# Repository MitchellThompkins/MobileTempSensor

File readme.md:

## Description

This contains all of the required documents to create a handheld temperature and humidity sensor.

### Current revision of the PCB:

### The populated board and finished design:

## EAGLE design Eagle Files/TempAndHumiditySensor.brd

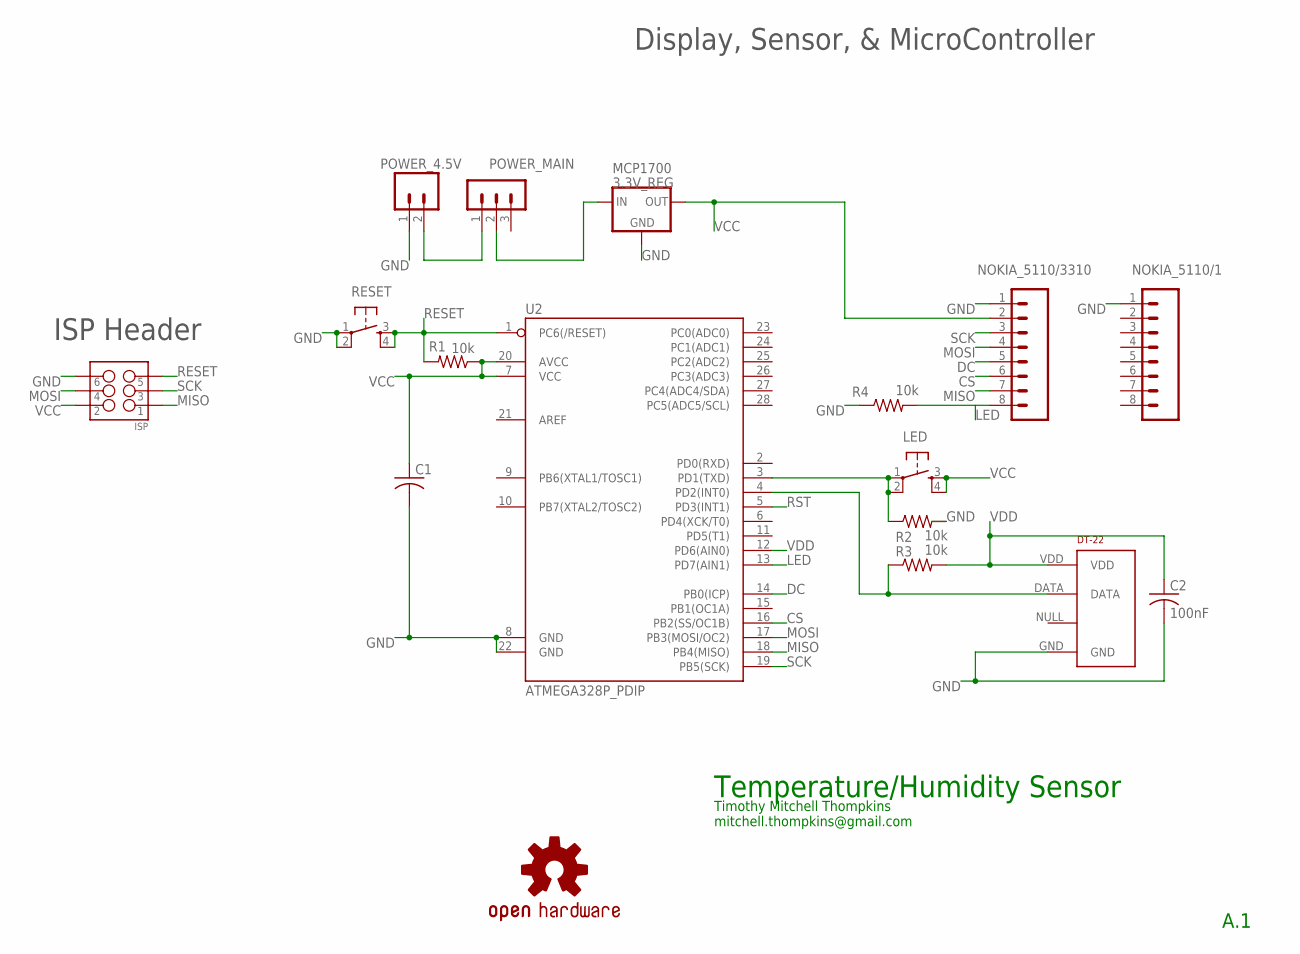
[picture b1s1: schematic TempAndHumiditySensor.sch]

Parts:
C1: C-US025-040X050; C025-040X050
C2: 100nF; C025-040X050
DT-22: RHT03_DHT-22_AM2302RA; RHT03_DHT-22/RA
ISP: M03X2POGO_PINS; 2X3_POGO
LED: RESET; TACTILE-PTH
LOGO2: OSHW-LOGOS; OSHW-LOGO-S
MCP1700: 3.3V_REG; TO92-INLINE
NOKIA_5110/1, NOKIA_5110/3310: M08; 1X08_PIN1_NO_SILK
POWER_4.5V: M02LOCK_LONGPADS; 1X02_LOCK_LONGPADS
POWER_MAIN: MA03-1
R1, R2, R3, R4: 10k; 0204/7
RESET: RESET; TACTILE-PTH
U2: ATMEGA328P_PDIP; DIL28-3

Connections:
CS: NOKIA_5110/3310.6, U2.16 (PB2(SS/OC1B))
DC: NOKIA_5110/3310.5, U2.14 (PB0(ICP))
GND: C1.2, C2.2, DT-22.GND, ISP.P$6 (6), MCP1700.1 (GND), NOKIA_5110/1.1, NOKIA_5110/3310.1, POWER_4.5V.1, R2.2, R4.1, RESET.1, RESET.2, U2.8 (GND), U2.22 (GND)
LED: NOKIA_5110/3310.8, R4.2, U2.13 (PD7(AIN1))
MISO: ISP.P$1 (1), NOKIA_5110/3310.7, U2.18 (PB4(MISO))
MOSI: ISP.P$4 (4), NOKIA_5110/3310.4, U2.17 (PB3(MOSI/OC2))
unnamed: POWER_4.5V.2, POWER_MAIN.1
unnamed: MCP1700.2 (IN), POWER_MAIN.2
unnamed: LED.1, LED.2, R2.1, U2.3 (PD1(TXD))
unnamed: DT-22.DATA, R3.1, U2.4 (PD2(INT0))
RESET: ISP.P$5 (5), R1.2, RESET.3, RESET.4, U2.1 (PC6(/RESET))
RST: U2.5 (PD3(INT1))
SCK: ISP.P$3 (3), NOKIA_5110/3310.3, U2.19 (PB5(SCK))
VCC: C1.1, ISP.P$2 (2), LED.3, LED.4, MCP1700.3 (OUT), NOKIA_5110/3310.2, R1.1, U2.7 (VCC), U2.20 (AVCC)
VDD: C2.1, DT-22.VDD, R3.2, U2.12 (PD6(AIN0))

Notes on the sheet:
Timothy Mitchell Thompkins mitchell.thompkins@gmail.com
Temperature/Humidity Sensor
A.1
ISP Header
Display, Sensor, & MicroController

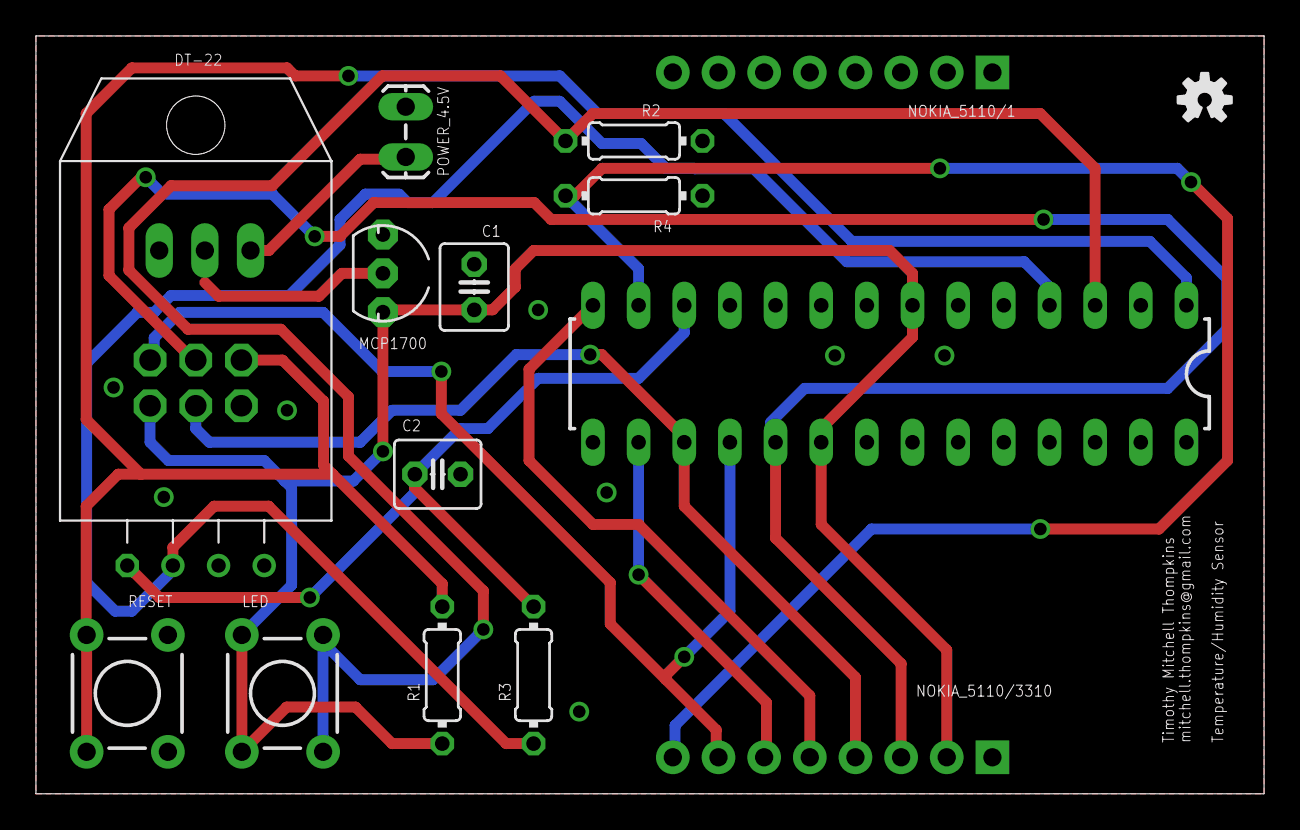
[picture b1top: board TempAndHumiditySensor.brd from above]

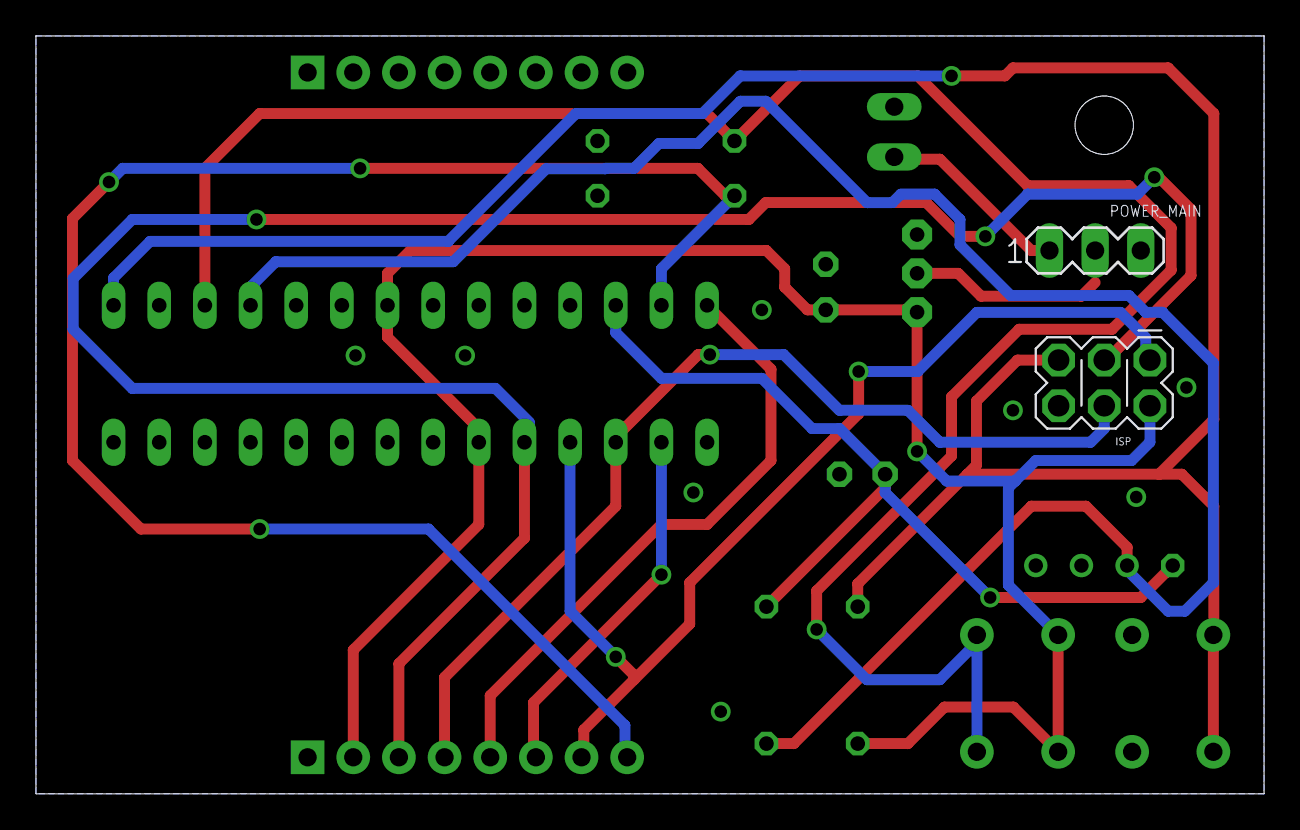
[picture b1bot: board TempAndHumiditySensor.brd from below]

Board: 2 copper layers, 68.3 x 42.2 mm, 17 parts (2 on the bottom side), 14 nets.

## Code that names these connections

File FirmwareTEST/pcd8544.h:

/*
 *
 * Name         :  pcd8544.h
 *
 * Description  :  This is header file for the PCD8544 graphic LCD driver.
 *                 Based on the code written by Sylvain Bissonette
 *
 * Author       :  Fandi Gunawan <fandigunawan@gmail.com>
 * Website      :  http://fandigunawan.wordpress.com
 *
 * Credit       :  Sylvain Bissonette (2003)
 *                 Louis Frigon (2003)
 *
 * License      :  GPL v. 3
 *
 * Compiler     :  WinAVR, GCC for AVR platform
 *                 Tested version :
 *                 - 20070525
 *                 - 20071221
 *                 - 20081225
 * Compiler note:  Please be aware of using older/newer version since WinAVR
 *                 is in extensive development. Please compile with parameter -O1
 *
 * History      :
 * Please refer to pcd8544.c
 */

#ifndef _PCD8544_H_
#define _PCD8544_H_

/* General constants for driver */
#define FALSE                      0
#define TRUE                       1

/* For return value */
#define OK                         0
#define OUT_OF_BORDER              1
#define OK_WITH_WRAP               2


#define LCD_X_RES                  84    /* x resolution */
#define LCD_Y_RES                  48    /* y resolution */
#define EMPTY_SPACE_BARS           2
#define BAR_X                      5
#define BAR_Y                      38

/* LCD Port */
#define LCD_PORT                   PORTB
#define LCD_DDR                    DDRB

/* ATMega8 port pinout for LCD. */
/* 0.2.6 bug, fixed */
#define LCD_DC_PIN                 PB0  /* Pin 0 */
#define LCD_CE_PIN                 PB2  /* Pin 2 */
#define SPI_MOSI_PIN               PB3  /* Pin 3 */
#define LCD_RST_PIN                PB4  /* Pin 4 */
#define SPI_CLK_PIN                PB5  /* Pin 5 */

/* Cache size in bytes ( 84 * 48 ) / 8 = 504 bytes */
#define LCD_CACHE_SIZE             ( ( LCD_X_RES * LCD_Y_RES ) / 8)

/* Type definition */
typedef char                       bool;
typedef unsigned char              byte;
typedef unsigned int               word;

/* Enumeration */
typedef enum
{
    LCD_CMD  = 0,
    LCD_DATA = 1

} LcdCmdData;

typedef enum
{
    PIXEL_OFF =  0,
    PIXEL_ON  =  1,
    PIXEL_XOR =  2

} LcdPixelMode;

typedef enum
{
    FONT_1X = 1,
    FONT_2X = 2

} LcdFontSize;

/* Function prototypes */
void LcdInit       ( void );
void LcdDeinit	   ( void );
void LcdClear      ( void );
void LcdUpdate     ( void );
void LcdImage      ( const byte *imageData );
void LcdContrast   ( byte contrast );
byte LcdGotoXYFont ( byte x, byte y );
byte LcdChr        ( LcdFontSize size, byte ch );
byte LcdStr        ( LcdFontSize size, byte dataArray[] );
byte LcdFStr       ( LcdFontSize size, const byte *dataPtr );
byte LcdPixel      ( byte x, byte y, LcdPixelMode mode );
byte LcdLine       ( byte x1, byte x2, byte y1, byte y2, LcdPixelMode mode );
byte LcdRect       ( byte x1, byte x2, byte y1, byte y2, LcdPixelMode mode );
byte LcdSingleBar  ( byte baseX, byte baseY, byte height, byte width, LcdPixelMode mode );
byte LcdBars       ( byte data[], byte numbBars, byte width, byte multiplier );



/*
 * Character lookup table code was taken from the work of Sylvain Bissonette
 * This table defines the standard ASCII characters in a 5x7 dot format.
 */
static const byte FontLookup [][5] PROGMEM=
{
    { 0x00, 0x00, 0x00, 0x00, 0x00 },   /* space */
    { 0x00, 0x00, 0x2f, 0x00, 0x00 },   /* ! */
    { 0x00, 0x07, 0x00, 0x07, 0x00 },   /* " */
    { 0x14, 0x7f, 0x14, 0x7f, 0x14 },   /* # */
    { 0x24, 0x2a, 0x7f, 0x2a, 0x12 },   /* $ */
    { 0xc4, 0xc8, 0x10, 0x26, 0x46 },   /* % */
    { 0x36, 0x49, 0x55, 0x22, 0x50 },   /* & */
    { 0x00, 0x05, 0x03, 0x00, 0x00 },   /* ' */
    { 0x00, 0x1c, 0x22, 0x41, 0x00 },   /* ( */
    { 0x00, 0x41, 0x22, 0x1c, 0x00 },   /* ) */
    { 0x14, 0x08, 0x3E, 0x08, 0x14 },   /* * */
    { 0x08, 0x08, 0x3E, 0x08, 0x08 },   /* + */
    { 0x00, 0x00, 0x50, 0x30, 0x00 },   /* , */
    { 0x10, 0x10, 0x10, 0x10, 0x10 },   /* - */
    { 0x00, 0x60, 0x60, 0x00, 0x00 },   /* . */
    { 0x20, 0x10, 0x08, 0x04, 0x02 },   /* / */
    { 0x3E, 0x51, 0x49, 0x45, 0x3E },   /* 0 */
    { 0x00, 0x42, 0x7F, 0x40, 0x00 },   /* 1 */
    { 0x42, 0x61, 0x51, 0x49, 0x46 },   /* 2 */
    { 0x21, 0x41, 0x45, 0x4B, 0x31 },   /* 3 */
    { 0x18, 0x14, 0x12, 0x7F, 0x10 },   /* 4 */
    { 0x27, 0x45, 0x45, 0x45, 0x39 },   /* 5 */
    { 0x3C, 0x4A, 0x49, 0x49, 0x30 },   /* 6 */
    { 0x01, 0x71, 0x09, 0x05, 0x03 },   /* 7 */
    { 0x36, 0x49, 0x49, 0x49, 0x36 },   /* 8 */
    { 0x06, 0x49, 0x49, 0x29, 0x1E },   /* 9 */
    { 0x00, 0x36, 0x36, 0x00, 0x00 },   /* : */
    { 0x00, 0x56, 0x36, 0x00, 0x00 },   /* ; */
    { 0x08, 0x14, 0x22, 0x41, 0x00 },   /* < */
    { 0x14, 0x14, 0x14, 0x14, 0x14 },   /* = */
    { 0x00, 0x41, 0x22, 0x14, 0x08 },   /* > */
    { 0x02, 0x01, 0x51, 0x09, 0x06 },   /* ? */
    { 0x32, 0x49, 0x59, 0x51, 0x3E },   /* @ */
    { 0x7E, 0x11, 0x11, 0x11, 0x7E },   /* A */
    { 0x7F, 0x49, 0x49, 0x49, 0x36 },   /* B */
    { 0x3E, 0x41, 0x41, 0x41, 0x22 },   /* C */
    { 0x7F, 0x41, 0x41, 0x22, 0x1C },   /* D */
    { 0x7F, 0x49, 0x49, 0x49, 0x41 },   /* E */
    { 0x7F, 0x09, 0x09, 0x09, 0x01 },   /* F */
    { 0x3E, 0x41, 0x49, 0x49, 0x7A },   /* G */
    { 0x7F, 0x08, 0x08, 0x08, 0x7F },   /* H */
    { 0x00, 0x41, 0x7F, 0x41, 0x00 },   /* I */
    { 0x20, 0x40, 0x41, 0x3F, 0x01 },   /* J */
    { 0x7F, 0x08, 0x14, 0x22, 0x41 },   /* K */
    { 0x7F, 0x40, 0x40, 0x40, 0x40 },   /* L */
    { 0x7F, 0x02, 0x0C, 0x02, 0x7F },   /* M */
    { 0x7F, 0x04, 0x08, 0x10, 0x7F },   /* N */
    { 0x3E, 0x41, 0x41, 0x41, 0x3E },   /* O */
    { 0x7F, 0x09, 0x09, 0x09, 0x06 },   /* P */
    { 0x3E, 0x41, 0x51, 0x21, 0x5E },   /* Q */
    { 0x7F, 0x09, 0x19, 0x29, 0x46 },   /* R */
    { 0x46, 0x49, 0x49, 0x49, 0x31 },   /* S */
    { 0x01, 0x01, 0x7F, 0x01, 0x01 },   /* T */
    { 0x3F, 0x40, 0x40, 0x40, 0x3F },   /* U */
    { 0x1F, 0x20, 0x40, 0x20, 0x1F },   /* V */
    { 0x3F, 0x40, 0x38, 0x40, 0x3F },   /* W */
    { 0x63, 0x14, 0x08, 0x14, 0x63 },   /* X */
    { 0x07, 0x08, 0x70, 0x08, 0x07 },   /* Y */
    { 0x61, 0x51, 0x49, 0x45, 0x43 },   /* Z */
    { 0x00, 0x7F, 0x41, 0x41, 0x00 },   /* [ */
    { 0x55, 0x2A, 0x55, 0x2A, 0x55 },   /* "Yen" */
    { 0x00, 0x41, 0x41, 0x7F, 0x00 },   /* ] */
    { 0x04, 0x02, 0x01, 0x02, 0x04 },   /* ^ */
    { 0x40, 0x40, 0x40, 0x40, 0x40 },   /* _ */
    { 0x00, 0x01, 0x02, 0x04, 0x00 },   /* ' */
    { 0x20, 0x54, 0x54, 0x54, 0x78 },   /* a */
    { 0x7F, 0x48, 0x44, 0x44, 0x38 },   /* b */
    { 0x38, 0x44, 0x44, 0x44, 0x20 },   /* c */
    { 0x38, 0x44, 0x44, 0x48, 0x7F },   /* d */
    { 0x38, 0x54, 0x54, 0x54, 0x18 },   /* e */
    { 0x08, 0x7E, 0x09, 0x01, 0x02 },   /* f */
    { 0x0C, 0x52, 0x52, 0x52, 0x3E },   /* g */
    { 0x7F, 0x08, 0x04, 0x04, 0x78 },   /* h */
    { 0x00, 0x44, 0x7D, 0x40, 0x00 },   /* i */
    { 0x20, 0x40, 0x44, 0x3D, 0x00 },   /* j */
    { 0x7F, 0x10, 0x28, 0x44, 0x00 },   /* k */
    { 0x00, 0x41, 0x7F, 0x40, 0x00 },   /* l */
    { 0x7C, 0x04, 0x18, 0x04, 0x78 },   /* m */
    { 0x7C, 0x08, 0x04, 0x04, 0x78 },   /* n */
    { 0x38, 0x44, 0x44, 0x44, 0x38 },   /* o */
    { 0x7C, 0x14, 0x14, 0x14, 0x08 },   /* p */
    { 0x08, 0x14, 0x14, 0x18, 0x7C },   /* q */
    { 0x7C, 0x08, 0x04, 0x04, 0x08 },   /* r */
    { 0x48, 0x54, 0x54, 0x54, 0x20 },   /* s */
    { 0x04, 0x3F, 0x44, 0x40, 0x20 },   /* t */
    { 0x3C, 0x40, 0x40, 0x20, 0x7C },   /* u */
    { 0x1C, 0x20, 0x40, 0x20, 0x1C },   /* v */
    { 0x3C, 0x40, 0x30, 0x40, 0x3C },   /* w */
    { 0x44, 0x28, 0x10, 0x28, 0x44 },   /* x */
    { 0x0C, 0x50, 0x50, 0x50, 0x3C },   /* y */
    { 0x44, 0x64, 0x54, 0x4C, 0x44 }    /* z */
};

#endif  /*  _PCD8544_H_ */

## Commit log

2014-11-06 Added Image Folder
2014-11-06 Trying to get Firmware Foler properly linked
2014-12-12 Committing changes made a while ago 12/11/2014
2016-01-08 Added Image

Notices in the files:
parts and their libraries:
SparkFun: Licensing: CC v3.0 Share-Alike You are welcome to use this library for commercial purposes.
SparkFun-Connectors: Licensing: Creative Commons ShareAlike 4.0 International - https://creativecommons.org/licenses/by-sa/4.0
